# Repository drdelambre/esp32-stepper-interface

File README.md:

_[ note: this readme is in jest, but captures the spirit of the project in lieu of actual documentation ]_

## embedded interface
Embedded Interface aims to reduce the complexity of starting a new mechatronic project. From reconciling sensor communication protocols, to convincing the hardware team that you _only need one more_ wire routed through a chassis, a lot of time is wasted reinventing a communications stack that essentially turns raw sensor data into a packet that can be digested somewhere else. Why can’t we just plug in a sensor and start focusing on what it is we are trying to build, instead of rewriting a service discovery protocol for the n-th time when we just wanted to get a UART module into ROS? Taking a page from both ROS and distributed system design, these building blocks aim to push the complexity into reusable edge nodes that allow you to prototype faster, spend more time focusing on your use-case, and ship a more reliable product.

## how it works:
Each integration is composed of a sensor board, a reusable communications stack, and a power bus convertor.

[ image showing squares with examples of each ]

The sensor board contains the discrete circuitry required for your sensing application. Currently, we are developing these reference designs:
* temperature controller: couples a thermo couple with a pid controlled solid state relay. [done]
* Stepper driver: a high resolution stepper driver based off of the TMC2130 [ done ]
* VESC driver: regenerative braking and full system diagnostics come from this brushless motor controller.
* Camera Controller: create full resolution RTP streams on your network, or sample single images at will.
* Battery monitor: Watch your cell voltages change under load and make sure you still have enough juice to get home.

The communications stack is responsible for service discovery, network configuration, firmware updates, and mitigating communication between your bus and the sensor board. Found out that you can’t use wifi in your new aluminum chassis? Swap it out for the ethernet version and continue with your day. On the roadmap there are these designs:
* mqtt / wifi: configure your wireless network through bluetooth, then let mDNS configure the mqtt broker. [done]
* mqtt / ethernet: similar to the wifi version, but hardwired and configured with DHCP.
* EtherCAT: For you latency sensitive users.
* USB: sometimes you just want to test something.

The power bus convertor allows you to run a single power bus through your application, and converts that line voltage into whatever your sensor requires, all while providing reversed polarity and short circuit protection. Need to change the battery voltage to drive more torque out of your brushless motors? Just swap out the power bus convertors on your sensors, and plug in that bigger battery!
* These come in all shapes and sizes, but I needed a bullet point for consistency.

## example application
A wireless reflow oven with an automatic door

[ insert image of a temp controller, stepper driver, and mqtt broker ]

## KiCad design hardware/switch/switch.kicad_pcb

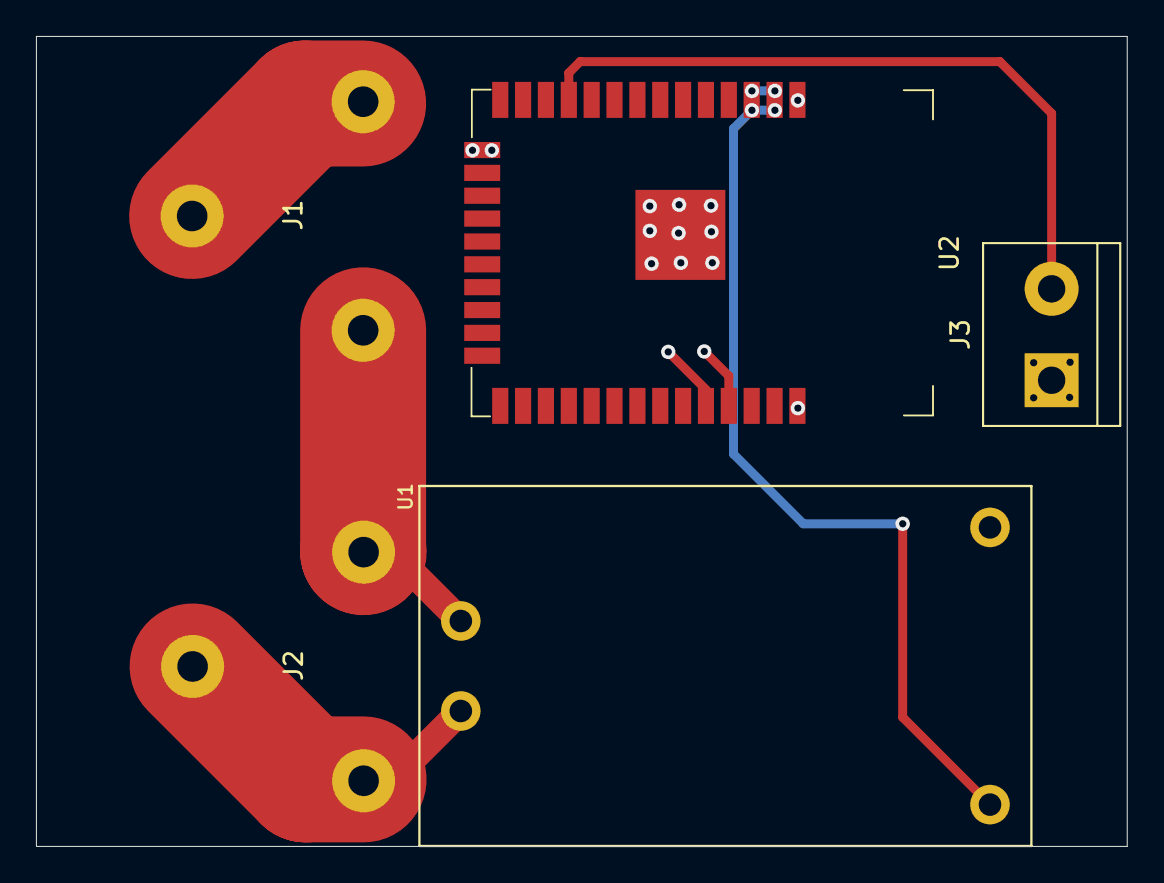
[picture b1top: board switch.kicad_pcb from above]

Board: 2 copper layers, 60.6 x 45.0 mm, 5 parts (0 on the bottom side), 6 nets.

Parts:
J1, J2: Conn_01x03; PhoenixContact-1017515
J3: Screw_Terminal_01x02; TerminalBlock_bornier-2_P5.08mm
U1: VAL*; HLK-PM03
U2: ESP32-WROOM; ESP32-WROOM-32D

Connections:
+3V3: U1.4, U2.2, U2.3
GND: J3.1, U1.3, U2.1, U2.15, U2.38, U2.39
unnamed: J1.1, J1.2
unnamed: J1.3, J2.1, U1.1
unnamed: J2.2, J2.3, U1.2
unnamed: J3.2, U2.11

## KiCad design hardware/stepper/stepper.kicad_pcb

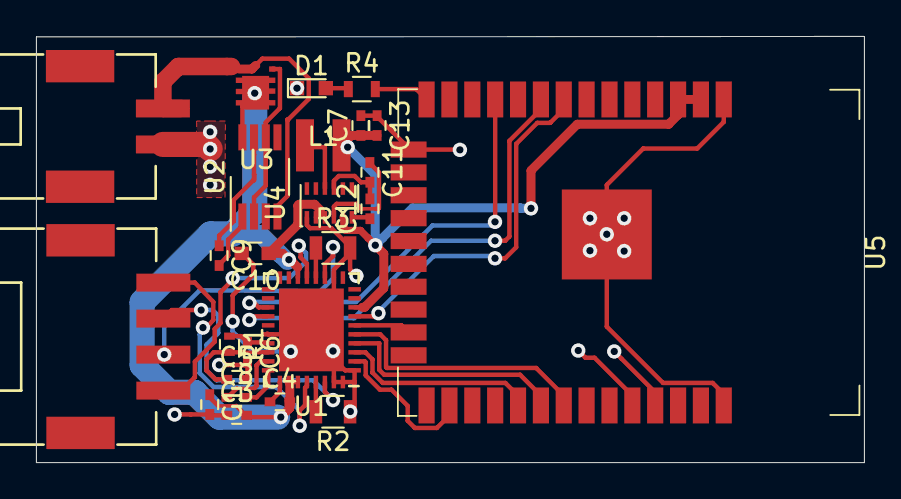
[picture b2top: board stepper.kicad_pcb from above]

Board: 2 copper layers, 46.0 x 23.7 mm, 25 parts (0 on the bottom side), 32 nets.

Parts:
C1, C3, C4, C7: 100n/50V; C_0402
C5: 470n/10V; C_0402
C6: 4u7/10V; C_0402
C8: 22n; C_0402
C9: 2.2u/16V; C_0402
C10: 2.2u/50V; C_0603
C11: 1u/16V; C_0402
C12: 3300p/16V; C_0402
C13: 22u/16V; C_0402
D1: LED; LED_0603
J1: Conn_01x04; SM04B-PASS
J2: Conn_01x02; SM02B-PASS
L1: 15u; XFL3012-153MEB
R1: 2R2; R_0402
R2, R3: R0805/0R11; R_0805
R4: 1K; R_0603
U1: TMC2130; QFN-36-1EP_5x6mm_Pitch0.5mm
U2: LM74610; VSSOP-8_3.0x3.0mm_Pitch0.65mm
U3: SI5448DU; Si5448DU
U4: MAX17502E; TDFN-12_2x3mm_Pitch0.5mm
U5: ESP32-WROOM; ESP32-WROOM-32D

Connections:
CS: U1.2, U5.26
DIR: U1.7, U5.8
EN: U1.22, U5.9
GND: C1.2, C3.1, C5.2, C6.2, C7.2, C10.2, C13.1, D1.1, J2.2, R2.1, R3.2, U1.1, U1.12, U1.24, U1.35, U1.36, U1.37, U4.1, U5.1, U5.15, U5.38, U5.39
GNDA: C11.2, C12.2, U4.9
MISO: U1.5, U5.31
MOSI: U1.4, U5.30
unnamed: C4.1, U1.29
unnamed: C5.1, R1.2, U1.26
unnamed: C6.1, R1.1, U1.25
unnamed: C8.1, U1.27
unnamed: C8.2, U1.28
unnamed: C9.1, U2.7
unnamed: C9.2, U2.1
unnamed: C11.1, U4.4
unnamed: C12.1, U4.6
unnamed: D1.2, R4.1
unnamed: J1.1, U1.32
unnamed: J1.2, U1.34
unnamed: J1.3, U1.13
unnamed: J1.4, U1.15
unnamed: J2.1, U2.4, U3.5, U3.9
unnamed: L1.1, U4.10
unnamed: R2.2, U1.33
unnamed: R3.1, U1.14
unnamed: R4.2, U5.14
unnamed: U2.2, U2.6, U3.4
SCK: U1.3, U5.29
STALL: U1.21, U5.11
STEP: U1.6, U5.23
VIO: C7.1, C13.2, L1.2, U1.8, U4.5, U5.2, U5.3
VM: C1.1, C3.2, C4.2, C10.1, U1.16, U1.30, U1.31, U2.8, U3.0, U3.1, U3.2, U3.3, U3.6, U3.7, U3.8, U4.2, U4.3

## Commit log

2019-04-12 migration from gitlab
2019-04-14 atomizing switch component
2019-04-16 stash for vesc
2019-04-17 compiles now
2019-04-29 better temp controller mqtt interface
2019-04-29 Porting vesc code (#1)
    * compiles now
    * better temp controller mqtt interface
2019-05-01 moving init into node
2019-05-01 removing headers
